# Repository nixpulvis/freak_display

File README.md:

# synth

## Primary Parts

- Arduino Mini Pro
- MSEQ7 (7 band spectrum analyzer)
- 168 (28x6) Addressable LEDs

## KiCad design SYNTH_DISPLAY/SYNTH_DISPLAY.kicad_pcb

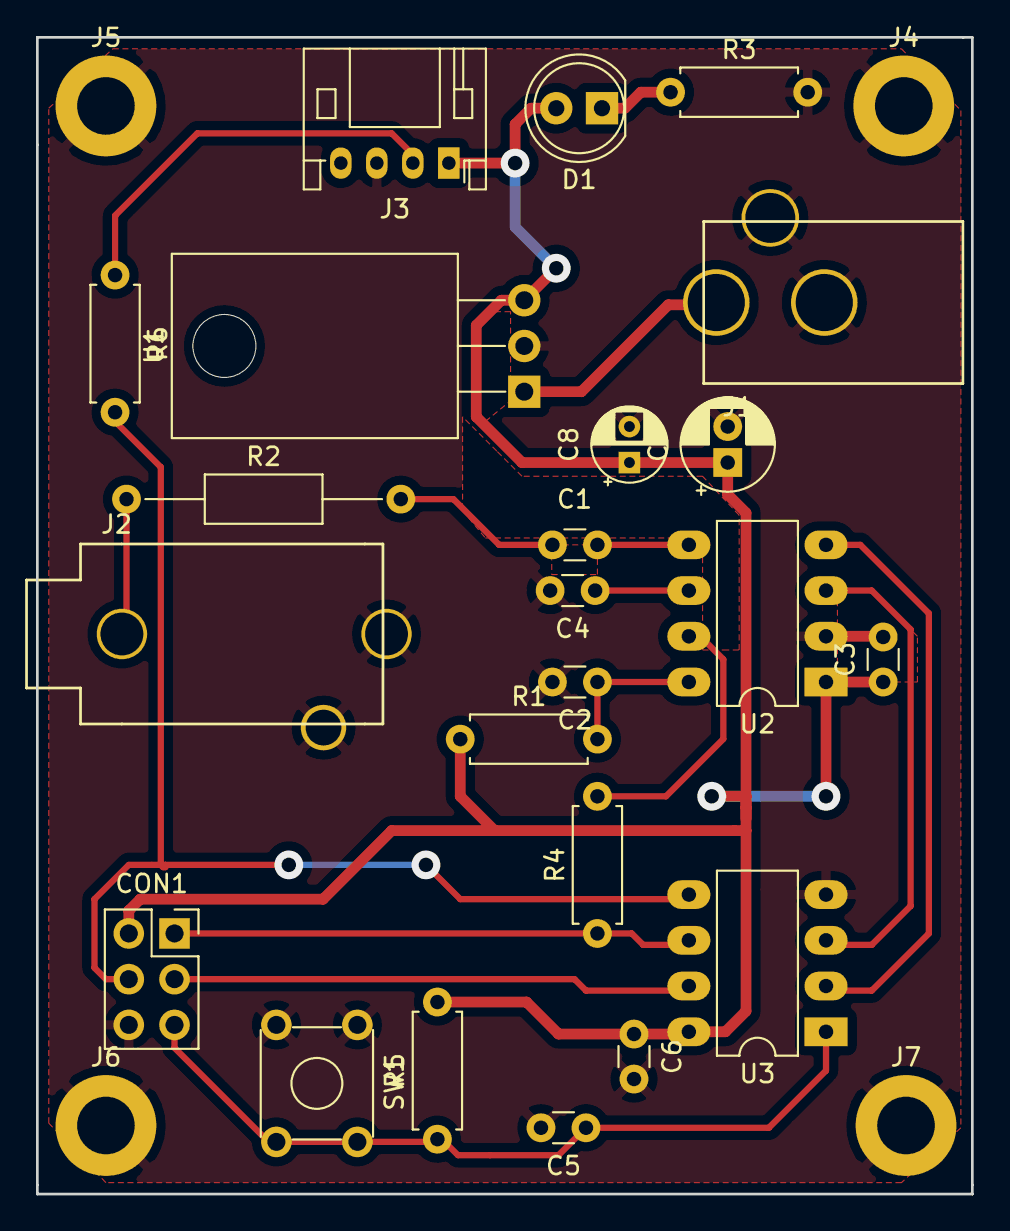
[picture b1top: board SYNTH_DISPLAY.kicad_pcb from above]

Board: 2 copper layers, 51.9 x 64.3 mm, 27 parts (0 on the bottom side), 17 nets.

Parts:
C1: 0.01u; C_Disc_D3.0mm_W1.6mm_P2.50mm
C2: 33p; C_Disc_D3.0mm_W1.6mm_P2.50mm
C3, C4, C5: 0.1u; C_Disc_D3.0mm_W1.6mm_P2.50mm
C6: 0.1; C_Disc_D3.0mm_W1.6mm_P2.50mm
C7: 100u; CP_Radial_D5.0mm_P2.00mm
C8: 10u; CP_Radial_D4.0mm_P2.00mm
CON1: AVR-ISP-6; PinSocket_2x03_P2.54mm_Vertical
D1: LED_Small; LED_D5.0mm
J1: Barrel_Jack; PJ-002A_HANDDRILL
J2: Audio-Jack-3; MJ-3536N_HANDDRILL
J3: Conn_01x04; JST_PH_S4B-PH-K_1x04_P2.00mm_Horizontal
J4, J5, J6, J7: Conn_01x01; MountingHole_3.2mm_M3_DIN965_Pad
R1: 200k; R_Axial_DIN0207_L6.3mm_D2.5mm_P7.62mm_Horizontal
R2: 22k; R_Axial_DIN0207_L6.3mm_D2.5mm_P15.24mm_Horizontal
R3: 470; R_Axial_DIN0207_L6.3mm_D2.5mm_P7.62mm_Horizontal
R4, R5, R6: 4.7k; R_Axial_DIN0207_L6.3mm_D2.5mm_P7.62mm_Horizontal
SW1: SW_Push_Dual; SW_TH_Tactile_Omron_B3F-10xx
U1: L7805; TO-220_Horizontal
U2: MSGEQ7; DIP-8_W7.62mm_LongPads
U3: ATTINY85-20PU; DIP-8_W7.62mm_LongPads

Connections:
+5V: C3.1, C6.1, C7.1, C8.1, CON1.2, D1.2, J3.1, R1.1, R5.2, U1.3, U2.1, U3.8
/DISP: J3.2, R6.1
/EQ_OUT: U2.3, U3.3
/EQ_RST: R4.2, U2.7
/MISO: CON1.1, R4.1, U3.6
/MOSI: CON1.4, R6.2, U3.5
/RST: C5.1, CON1.5, R5.1, SW1.2, SW1.4, U3.1
/SCK: CON1.3, U3.7
/STROBE: U2.4, U3.2
GND: C2.2, C3.2, C4.2, C5.2, C6.2, C7.2, C8.2, CON1.6, J1.2, J1.3, J2.2, J2.3, J3.3, J4.1, J5.1, J6.1, J7.1, R3.2, SW1.1, SW1.3, U1.2, U2.2, U3.4
unnamed: C1.1, U2.5
unnamed: C1.2, R2.2
unnamed: C2.1, R1.2, U2.8
unnamed: C4.1, U2.6
unnamed: D1.1, R3.1
unnamed: J1.1, U1.1
unnamed: J2.1, R2.1

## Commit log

2017-05-22 Initial arduino code for 7 LED control.
2017-05-22 Use base values from a read without any noise.
2017-05-25 Update the base offset.
2017-05-25 Huge refactor, same functionality.
2017-05-25 Don't burn out the voltage regulator.
2017-05-25 Color by loudest band.
2017-05-26 Allow choosing color.xc
2017-05-26 Started the history buffer, BUGS EXIST LOL.
2017-05-26 Working, and conf.
2017-05-26 Remove done COMMENT.y
2017-05-29 FIx build for history.
2018-03-25 starting schematic
2018-03-25 first schematic attempt
2018-03-26 finished layout
2018-03-27 added display header, mounting holes, and moved connectors
2018-03-28 Schematic formatting and removing a no-connect
2018-04-10 Update page size.
2018-04-25 Adding the schematic PDF.
2018-04-25 changed from A4 to letter size sheet
2018-08-17 Starting RAW C work (arduino/ATTiny)
2021-08-04 Update pin mapping for proto v2
2021-08-04 Move Arduino code into it's own folder
2021-08-04 Update to use band/depth numbers.
2021-08-04 Fix inverted logic on HISTORY_TIME
2021-08-04 Small line cleanup
2021-08-04 Brighter
2021-08-04 Renaming
2021-08-05 Remove broken project (for now?)
